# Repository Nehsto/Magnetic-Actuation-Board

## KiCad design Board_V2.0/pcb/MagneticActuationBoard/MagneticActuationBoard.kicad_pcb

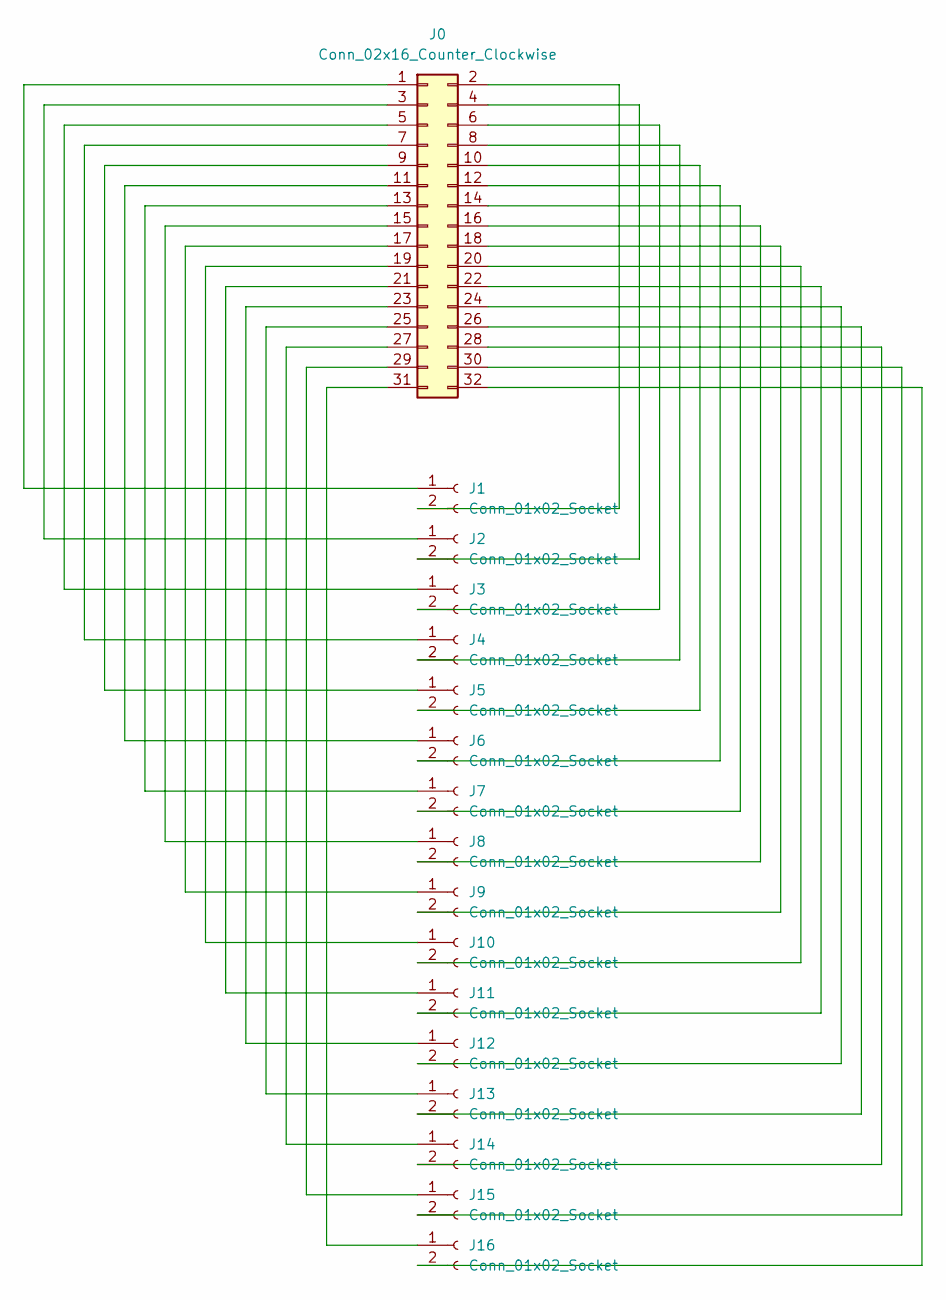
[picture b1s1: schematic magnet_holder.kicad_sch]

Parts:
J0: Conn_02x16_Counter_Clockwise; PinHeader_2x16_P2.54mm_Vertical
J1, J2, J3, J4, J5, J6, J7, J8, J9, J10, J11, J12, J13, J14, J15, J16: Conn_01x02_Socket; PinHeader_1x02_P2.54mm_Vertical

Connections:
unnamed: J0.1, J1.1
unnamed: J0.2, J1.2
unnamed: J0.3, J2.1
unnamed: J0.4, J2.2
unnamed: J0.5, J3.1
unnamed: J0.6, J3.2
unnamed: J0.7, J4.1
unnamed: J0.8, J4.2
unnamed: J0.9, J5.1
unnamed: J0.10, J5.2
unnamed: J0.11, J6.1
unnamed: J0.12, J6.2
unnamed: J0.13, J7.1
unnamed: J0.14, J7.2
unnamed: J0.15, J8.1
unnamed: J0.16, J8.2
unnamed: J0.17, J9.1
unnamed: J0.18, J9.2
unnamed: J0.19, J10.1
unnamed: J0.20, J10.2
unnamed: J0.21, J11.1
unnamed: J0.22, J11.2
unnamed: J0.23, J12.1
unnamed: J0.24, J12.2
unnamed: J0.25, J13.1
unnamed: J0.26, J13.2
unnamed: J0.27, J14.1
unnamed: J0.28, J14.2
unnamed: J0.29, J15.1
unnamed: J0.30, J15.2
unnamed: J0.31, J16.1
unnamed: J0.32, J16.2

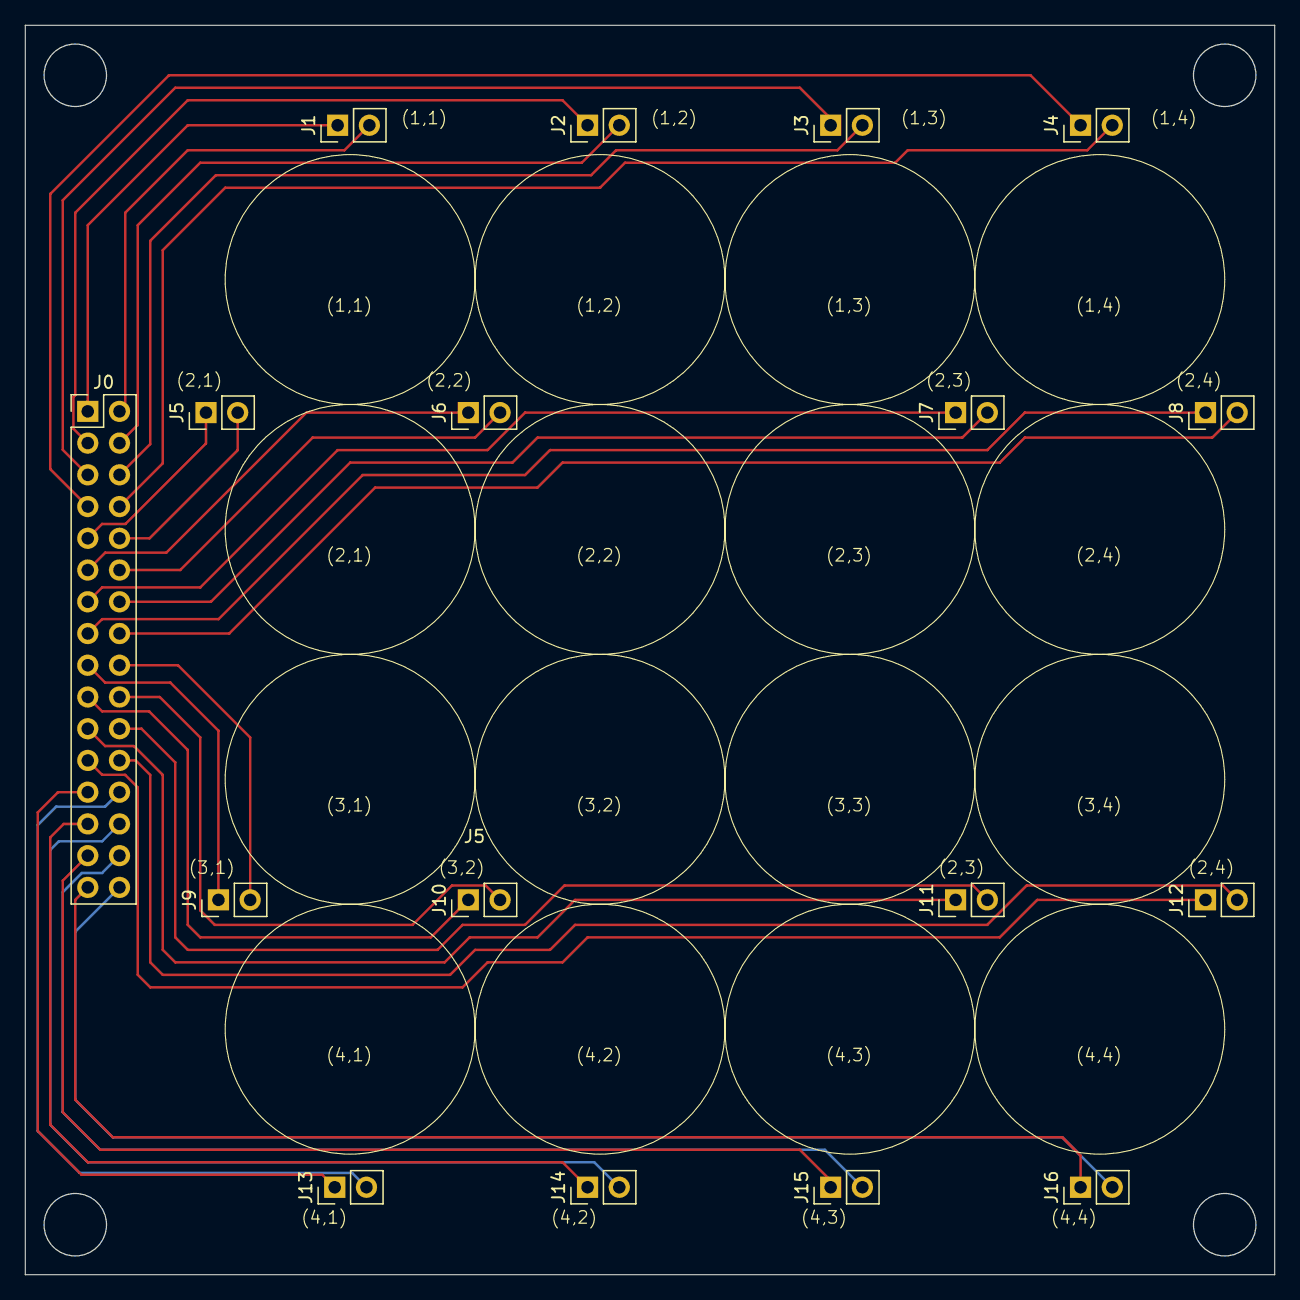
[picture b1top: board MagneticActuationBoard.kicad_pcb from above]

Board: 2 copper layers, 99.9 x 99.9 mm, 17 parts (0 on the bottom side), 32 nets.

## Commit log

2025-11-26 Uploading project
2025-11-26 Research Documentation
2025-11-26 I have been doing this git shit for too long and I don't get anywhere
2025-11-26 whatever
2025-11-26 tired
2025-11-26 tired2
